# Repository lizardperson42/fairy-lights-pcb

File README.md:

# fairy-lights-pcb

This repository contains the PCB design files for the fairy lights project.
The project is a set of fairy lights that is attached to a custom PCB and controlled by an ESP8266 microcontroller.
The PCB design files are created using KiCad.

## Parts

- This PCB (1 unit)
- [WeMos D1 Mini ESP8266](https://www.wemos.cc/en/latest/d1/d1_mini.html) (1 unit)
- DC barrel jack, 5.5mm OD, 2.1mm ID (1 unit)
- Screw terminals, 5mm pitch, 4-pin and/or 3-pin (up to 1 unit of each size)
- Pin header, 2.54mm pitch, 1x2 pins (1 unit)
- Pin headers, 2.54mm pitch, 1x4 pins and 2x4 pins (up to 1 unit each)
- WS2812B SMD LEDs (0 or 4 units)
- Vertical tactile push buttons (up to 2 units)
- THT resistors (10kΩ, 0 or 2 units)
- Power switch or jumper for the 2-pin header (1 unit)

### Notes

- The WeMos D1 Mini module can be mounted in various ways.
  The CAD model used here connects it via pin sockets and headers, permitting easy removal and reattachment.
- Any footprint-compatible barrel jack can be used.
- The screw terminals are used to attach connectors for the LED strands, which use wire-to-wire connectors.
- The 2-pin header is interposed between the power jack and the board's 5V rail.
  One can wire up a power switch to it or short it with a jumper.
  Without external power, the board is mostly useless.
  The PCB includes a free area for installing a power switch close to the front-panel buttons.
- The optional pin headers expose the pins of the WeMos D1 Mini module which are not used otherwise.
- The SMD LEDs are connected in a chain around the board; it is not useful to populate only some of them.
- The buttons are directly connected to the microcontroller's GPIO pins.
  - Button USER_A places the microcontroller into flashing mode when pressed during boot-up.
    After boot-up, it can be used to wake the microcontroller from standby mode.
  - Button USER_B cannot trigger standby wake-ups (its state can only be read by polling in software).
- The 4-pin header is connected to the microcontroller's conventional I²C bus pins and the 3.3V rail.
  The THT resistors, if populated, pull its clock and data lines up.
  Without the resistors, the 4-pin header simply exposes the two GPIO pins.
  Together with the 8-pin header's 5V pin, the 4-pin header can be used to drive another LED strand instead.

## Accessories

- 5V DC power supply, suitable current rating, pin positive, sleeve negative, matching the barrel jack
- WS2801 LED strand, JST SM 4-pin connector, particularly [this one](https://www.adafruit.com/product/322) (optional)
- WS2812B LED strand, JST SM 3-pin connector (optional)

The power supply needs to be rated to supply enough current to power the microcontroller and the LED strand(s).
The microcontroller can draw currents of up to 500mA, with typical consumption lower.
Consult your LED strands' user manuals for information about their current requirements.

> [!CAUTION]
> Do not attach the barrel jack and the microcontroller's USB connector simultaneously!

> [!IMPORTANT]
> This board powers the LED strands and on-board LEDs from the 5V rail but controls them using 3.3V signals straight from the ESP8266.
> This pushes the envelope of what their WS28xx driver chips are documented to support.
> This arrangement might work unreliably or not all.

## Connector and microcontroller pin overview

The PCB has the following connectors:

- J1: 5V DC power input, pin positive, sleeve negative
- J2: SPI LED strand connector, 5V power, 3.3V signals
  - Data line is tied to MCU pin D7 (GPIO13)
  - Clock line is tied to MCU pin D5 (GPIO14)
- J3: WS2812 LED strand connector, 5V power, 3.3V signals
  - Data line is tied to MCU pin D6 (GPIO12)
- J4: I²C connector, 3.3V power and signals
  - Data line is tied to MCU pin D2 (GPIO4)
  - Clock line is tied to MCU pin D1 (GPIO5)
- J5: Miscellaneous connector. Layout and MCU pin mapping:
  ```
   GND |1 2| RST
    5V |3 4| A0
  3.3V |5 6| D0
    RX |7 8| TX
  ```
  (pin D0 is also tied to button USER_B)
- SW1: Power switch, separates barrel jack from 5V rail when open.

The microcontroller's pins are used as follows:

| Name        | Function              | Connector               |
| ----------- | --------------------- | ----------------------- |
| GND         | Common ground         | J1; J2; J3; J4; J5; USB |
| 5V          | 5V rail               | J1; J2; J3; J5; USB     |
| 3.3V        | 3.3V rail             | J4; J5                  |
| RST         | Reset                 | J5                      |
| RX (GPIO3)  | UART receive          | J5; via USB             |
| TX (GPIO1)  | UART transmit         | J5; via USB             |
| A0 (ADC0)   | Analog input          | J5                      |
| D0 (GPIO16) | Button                | SW3 (USER_B)            |
| D1 (GPIO5)  | I²C clock             | J4                      |
| D2 (GPIO4)  | I²C data              | J4                      |
| D3 (GPIO0)  | Button; MCU flashing  | SW2 (USER_A)            |
| D4 (GPIO2)  | MCU module LED        | none                    |
| D5 (GPIO14) | SPI clock             | J2                      |
| D6 (GPIO12) | WS2812 data           | J3                      |
| D7 (GPIO13) | SPI data              | J2                      |
| D8 (GPIO15) | On-board WS2812B LEDs | none                    |

“USB” refers to the microcontroller module's USB port (5V, GND) or to its USB-to-serial converter chip (RX, TX).

## Case

A case design for this project is given as an OpenSCAD file in `fairy-lights-case/`.
It has been generated from the KiCad design files using [TurboCase](https://turbocase.org) and **manually edited**.
If some parts of the board are not to be populated, the corresponding case cutouts can be removed from the case source file.

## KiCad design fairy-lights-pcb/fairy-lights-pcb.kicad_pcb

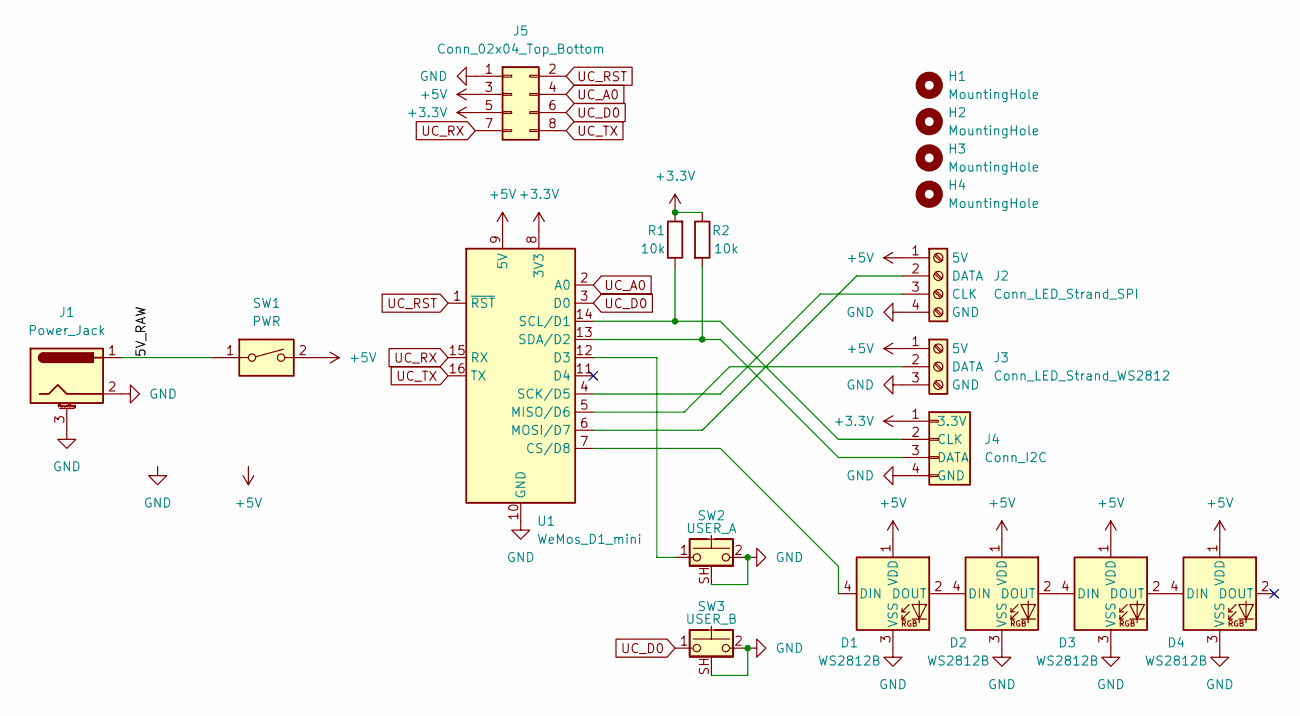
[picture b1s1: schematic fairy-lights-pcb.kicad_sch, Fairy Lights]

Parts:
D1, D2, D3, D4: WS2812B; LED_WS2812B_PLCC4_5.0x5.0mm_P3.2mm
H1, H2, H3, H4: MountingHole; MountingHole_2.2mm_M2
J1: Power_Jack; BarrelJack_Horizontal
J2: Conn_LED_Strand_SPI; TerminalBlock_LED_Strand_1x04
J3: Conn_LED_Strand_WS2812; TerminalBlock_LED_Strand_1x03
J4: Conn_I2C; PinHeader_1x04_P2.54mm_Vertical
J5: Conn_02x04_Top_Bottom; PinHeader_2x04_P2.54mm_Vertical
R1, R2: 10k; R_Axial_DIN0204_L3.6mm_D1.6mm_P7.62mm_Horizontal
SW1: PWR; PinHeader_Power
SW2: USER_A; SW_Tactile_SPST_Angled_PTS645Vx31-2LFS_SH
SW3: USER_B; SW_Tactile_SPST_Angled_PTS645Vx31-2LFS_SH
U1: WeMos_D1_mini; WEMOS_D1_mini_light

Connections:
+3.3V: J4.1 (3.3V), J5.5, R1.2, R2.1, U1.8 (3V3)
+5V: D1.1 (VDD), D2.1 (VDD), D3.1 (VDD), D4.1 (VDD), J2.1 (5V), J3.1 (5V), J5.3, SW1.2, U1.9 (5V)
/5V_RAW: J1.1, SW1.1
GND: D1.3 (VSS), D2.3 (VSS), D3.3 (VSS), D4.3 (VSS), J1.2, J1.3 (MP), J2.4 (GND), J3.3 (GND), J4.4 (GND), J5.1, SW2.2, SW2.SH (B), SW3.2, SW3.SH (B), U1.10 (GND)
unnamed: D1.4 (DIN), U1.7 (CS/D8)
unnamed: D1.2 (DOUT), D2.4 (DIN)
unnamed: D2.2 (DOUT), D3.4 (DIN)
unnamed: D3.2 (DOUT), D4.4 (DIN)
unnamed: J2.3 (CLK), U1.4 (SCK/D5)
unnamed: J2.2 (DATA), U1.6 (MOSI/D7)
unnamed: J3.2 (DATA), U1.5 (MISO/D6)
unnamed: J4.2 (CLK), R1.1, U1.14 (SCL/D1)
unnamed: J4.3 (DATA), R2.2, U1.13 (SDA/D2)
unnamed: SW2.1, U1.12 (D3)
UC_A0: J5.4, U1.2 (A0)
UC_D0: J5.6, SW3.1, U1.3 (D0)
UC_RST: J5.2, U1.1 (~RST)
UC_RX: J5.7, U1.15 (RX)
UC_TX: J5.8, U1.16 (TX)

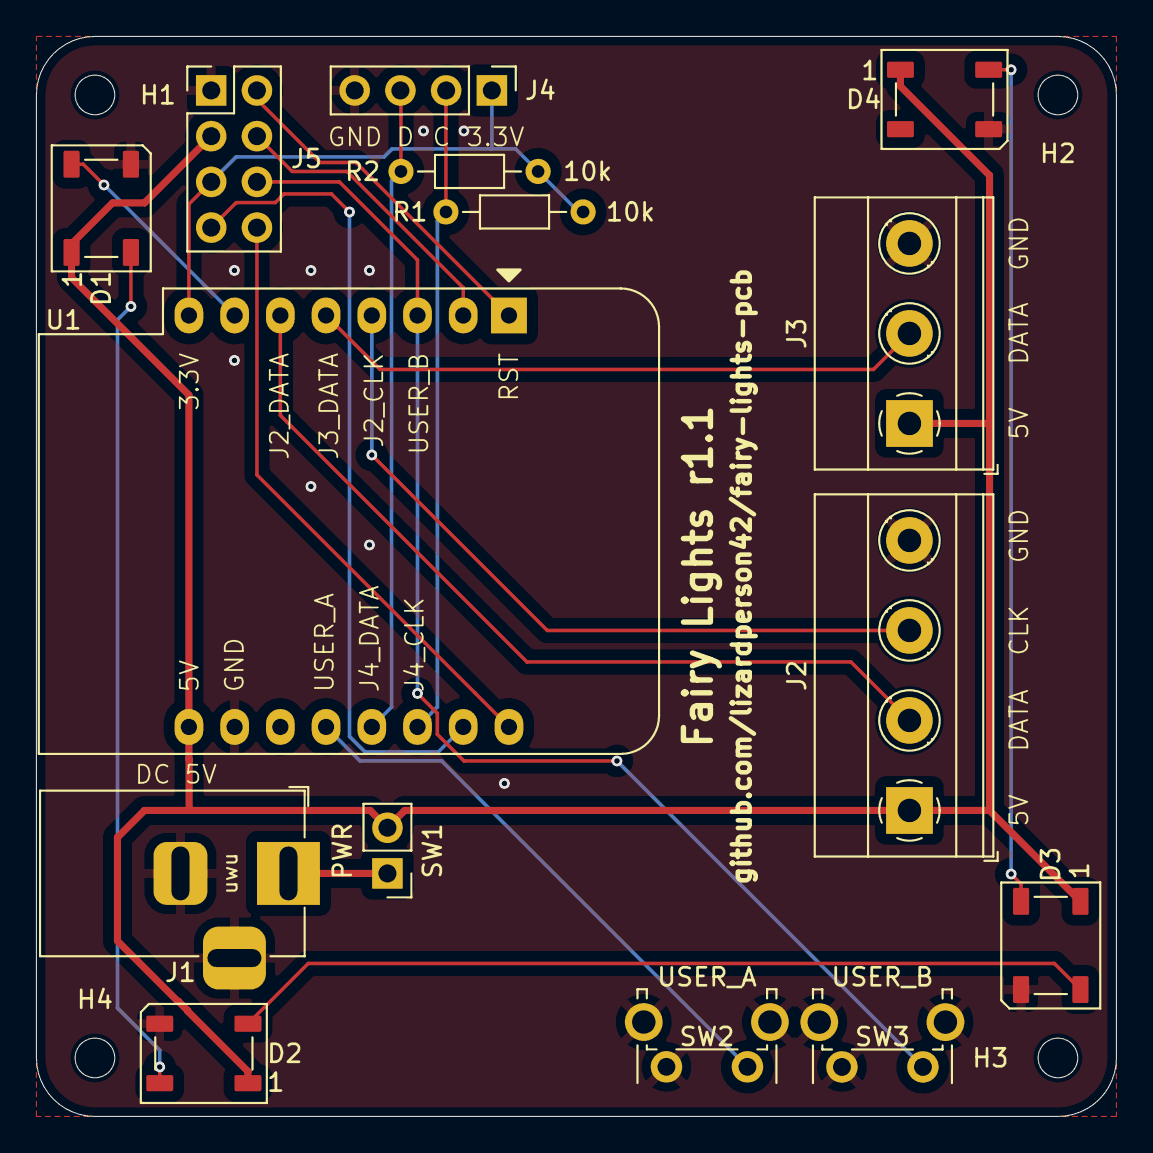
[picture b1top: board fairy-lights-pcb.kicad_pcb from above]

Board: 2 copper layers, 60.0 x 60.0 mm, 19 parts (0 on the bottom side), 19 nets.

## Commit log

2024-11-08 add parts
2024-11-08 init project in keycad
2024-11-08 move .gitignore
2024-11-08 add custom footprint & symbol libary
2024-11-08 change color of pcb
2024-11-08 add Custom footprint for TXS0108E
2024-11-08 add custom TXS0108EPW symbol
2024-11-08 Add .gitignore entry
2024-11-08 Add basic schematic
2024-11-08 Add board design and missing component footprints
2024-11-08 Add project settings
2024-11-08 Add resistor value and connector annotations
2024-11-09 Add more stuff
    - Two more output headers (functionally identical but one labeled like
    the first LED one and the second generically)
    - Header for a power switch (interposed between the power jack and the
    5V rail)
    - Header for a user switch/button (from a GPIO pin to ground)
    - User LED (from a GPIO pin to ground)
2024-11-09 Add labels; fix DRC complaints
2024-11-09 Avoid accidentally deleting mounting holes
2024-11-09 Increase thickness of 5V traces
    Also redoes all routing, because why not.
2024-11-10 add 3d model to chip
2024-11-10 update chip format
2024-11-10 add headers
2024-11-10 add sockets
2024-11-10 Add mounting holes to schematic
    This should mollify the design rule checker.
2024-11-10 Update level shifter in PCB to include 3D model
2024-11-10 Connect barrel jack mounting pin to ground
2024-11-10 Update user LED resistor value
2024-11-10 Tweak board dimensions
    They were *so close* to 6cm x 6cm, I couldn't (haha!) resist.
2024-11-10 Align PCB edges to centimeter boundaries
2024-11-10 Tweak level shifter model scale
    It's still not perfectly aligned, but at least the misalignment is less
    obvious.
2024-11-11 Make room for power switch
2024-11-11 Move mounting holes closer to rest of schematic
2024-11-11 Update pins and labels
    - All MCU pin silkscreen labels should now be correct.
    - The board title is updated to say "r(evision)" instead of "v(ersion)".
    - The middle pins of J3 and J4 are swapped for totally valid reasons
    (viz. schematic symmetry).
    - J4 is turned into a LED strand connector (such that its pin labels
    match the I2C functions of the corresponding MCU pins).
2024-11-11 Use different status LED
2024-11-13 Moar LEDs
    We're also considering yeeting or replacing the level shifter. Until we
    decide on what the replacement will be, I'll leave the current one in,
    with the understanding that one could substitute a pin-compatible and
    working replacement.
2024-11-17 Make the corners round
    The round parts of the corner edge cuts should be concentric with the
    mounting holes.
2024-11-23 Yeet level shifter; update interfaces
    - The level shifter we planned to use seems not to work on a breadboard.
    - Driving the LED controllers with 3.3V signals directly instead seems
    to work (although it is out-of-spec or barely at the boundary of what
    is in-spec).
    - LED strands are now attached via screw terminals. (Of course, one can
    choose not to populate them and solder wires directly to the pads
2024-11-23 Clarify README
2024-11-24 Ground the mounting pins of the buttons
    Also tweaks the location of the "5V 2A" label.
2024-11-24 Document parts and their usage in the README
2024-11-24 Tweak push button footprint
    Oh, hey, one can assign multiple footprint pads to the same schematic
    pin!
2024-11-24 Tweak MCU pin assignment
    - Swaps the J3_DATA and USER_B pins.
    - Now, all LED strand terminals and the I2C header are connected to GPIO
    pins with no strings (or, more accurately, random components on the
    MCU module) attached.
    - Button USER_B puts the MCU flash mode if pressed at boot-up. The same
    can be achieved via USB, but, I guess, it's useful for flashing in the
2024-11-24 Yeet obsolete components
2024-11-27 Fix component labels and positions
2024-11-27 Move USER_A button to pin D0
    This allows using it to wake out of deep sleep, and avoids interactions
    with the MCU module's built-in LED. The downside is that the pin has to
    be polled in software while the MCU is running.
2024-11-28 Update pull-up resistor values in README
2024-11-28 Add header for enabling deep sleep self-wakeup
2024-11-28 Revert "Add header for enabling deep sleep self-wakeup"
    It is not immediately useful if the same pin is also bound to a button,
    as this effectively turns the button into a reset button. I somewhat
    dislike the idea of placing a reset button right besides the "user"
    button.
    This reverts commit fe8c02f848e9494a1d23cb15ce68f1f10867b81e.
2024-11-28 Tweak button pin assignment
    Button USER_A is now assigned to pin D3, button USER_B to pin D0.
    Since this device is ultimately meant to be mains-powered, deep sleep
    support is not a priority (additionally, while the MCU is sleeping,
    the LED strand cannot quickly react to external requests delivered via
    WiFi). Therefore, now, button USER_A can act as a soft power button (it
    can even raise interrupts to wake from light sleep!) and also as a
2024-11-28 Document headers and MCU pins
2024-11-28 Add more notes to README
2024-11-29 Address review comments
2024-11-29 Clarify README further
2024-11-29 Fix button pin labels
2024-11-29 Tweak more PCB labels
2024-11-29 Add picture
2024-11-29 Add double-power warning
2024-11-29 Fix Markdown table
2024-12-08 add custom footprints including Turbocase footprints
2024-12-08 Update PCB to use Turbocase-enabled footprints
2024-12-08 update D1 mini footprint (KiCad 8.0.7)
2024-12-08 Update schematic and PCB to use correct D1 Mini
2024-12-09 Update USB port cutout
2024-12-09 Update barrel jack case cutout
2024-12-09 Add case cutouts for screw terminals
    Sheesh, those crimped wire ends are *huge*.
2024-12-09 Change layers of case properties
2024-12-10 Add case interior outline
2024-12-10 Change 360deg to 0deg
    Why didn't KiCad do that immediately but only now?..
2024-12-11 Update case modules
2024-12-16 Increase case margin
2025-01-16 Change power header to custom footprint
2025-01-17 Add case cutouts (and supports) for front panel
2025-01-22 Tweak screw terminal wire windows
2025-02-24 Add case
2025-02-24 Update revision number and GitHub URL
